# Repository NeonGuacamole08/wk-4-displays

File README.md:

# wk-4-displays

For the schematics and footprint, you will need:
| Component | KiCad Symbol | Footprint |
| :--- | :--- | :--- |
| **Microcontroller** | `Seeed_Studio_XIAO_Series:Seeed_XIAO_ESP32-C3` | `XIAO-ESP32-C3-SMD` |
| **LED Matrix Module Socket** | `Connector:Conn_01x05_Socket` | `Connector_PinSocket_2.54mm:PinSocket_1x05_P2.54mm_Vertical` |
| **Push Buttons (x3)** | `Switch:SW_Push` | `Button_Switch_THT:SW_PUSH_6mm` |
| **Rotary Encoder** | `Device:RotaryEncoder_Switch_MP` | `Rotary_Encoder:Rotary_Encoder_Alps_EC11E-Switch_Vertical_H20mm` |

I downloaded the footprints for my board here: https://github.com/Seeed-Studio/OPL_Kicad_Library/blob/master/Seeed%20Studio%20XIAO%20Series%20Library/XIAO-ESP32-C3-SMD.kicad_mod

## The Schematics:

- **A**: Add Symbol (Schematic Editor)
- **L**: Add Net Label (Schematic Editor)
- **E**: Edit Properties (Hover over any symbol or footprint and press E)

  1. Set up the XIAO ESP32-C3
   - Placed the XIAO ESP32-C3 microcontroller symbol on the canvas and assigned the official Seeed footprint (`XIAO-ESP32-C3-SMD`).

2. Added the LED Matrix Connector
   - Added a 5-pin female header socket (`Conn_01x05_Socket`) to connect the display module.
   - Connected hardware SPI pins (D7, D8, D10) plus power and ground using net labels to keep things clean.

3. Wired up the 10 µF Decoupling Capacitor
   - Placed a 10 µF capacitor across 5V and GND right near the matrix header to smooth out any power spikes from the LEDs.

4. Hooked up the 3 Push Buttons
   - Placed three push button symbols (`SW_Push`) with 6mm THT footprints.
   - Wired one side of each button to GND and the other side to individual GPIO pins (using `INPUT_PULLUP` in code so no extra resistors were needed).

5. Added the EC11 Rotary Encoder
   - Placed an EC11 encoder with switch symbol (`RotaryEncoder_Switch_MP`).
   - Wired pins A and B to digital GPIOs for rotation tracking, grounded common pin C and the mounting pins, and wired the built-in push switch (S1/S2) between a GPIO pin and GND.

6. Cleaned up with Net Labels
   - Used net labels across the whole sheet to keep the schematic tidy and easy to read without drawing long, crisscrossing wires.

## The PCB
Tip: You can use the "F" key to route your wiring using the shortest path
Trace your edge cuts, and you can even add some designs by using the image converter tool! 

You might need to play around with the size of your image!
1. Go to the image converter tool

2. Configure your image settings

3. Edit the size if needs be

4. Select "Footprint" as the output format (using the F.Cu layer), export to clipboard and paste in your PCB 

5. Paste on your PCB editor

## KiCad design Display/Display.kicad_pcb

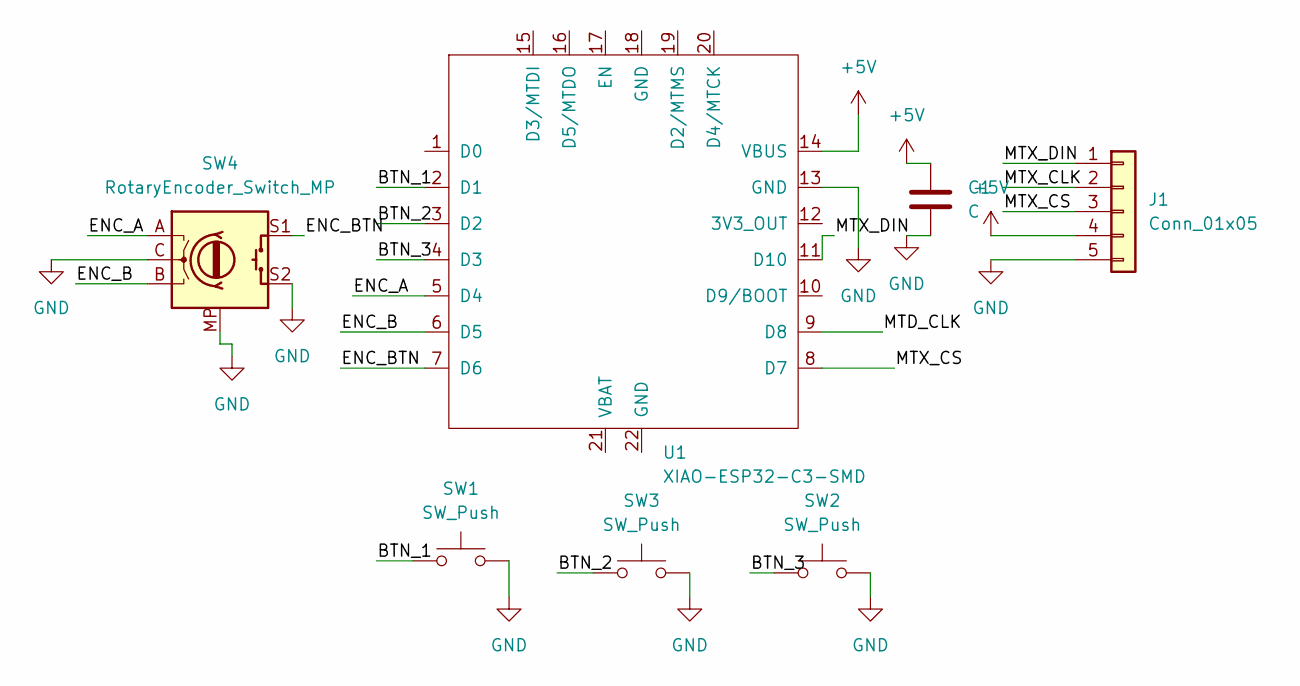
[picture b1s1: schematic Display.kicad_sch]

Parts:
C1: C; C_0805_2012Metric
J1: Conn_01x05; PinSocket_1x05_P2.54mm_Vertical
SW1, SW2, SW3: SW_Push; SW_PUSH_6mm
SW4: RotaryEncoder_Switch_MP; RotaryEncoder_Alps_EC11E-Switch_Vertical_H20mm
U1: XIAO-ESP32-C3-SMD

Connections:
+5V: C1.1, J1.4, U1.14 (VBUS)
/BTN_1: SW1.1, U1.2 (D1)
/BTN_2: SW3.1, U1.3 (D2)
/BTN_3: SW2.1, U1.4 (D3)
/ENC_A: SW4.A, U1.5 (D4)
/ENC_B: SW4.B, U1.6 (D5)
/ENC_BTN: SW4.S1, U1.7 (D6)
/MTD_CLK: U1.9 (D8)
/MTX_CLK: J1.2
/MTX_CS: J1.3, U1.8 (D7)
/MTX_DIN: J1.1, U1.11 (D10)
GND: C1.2, J1.5, SW1.2, SW2.2, SW3.2, SW4.C, SW4.MP, SW4.S2, U1.13 (GND)

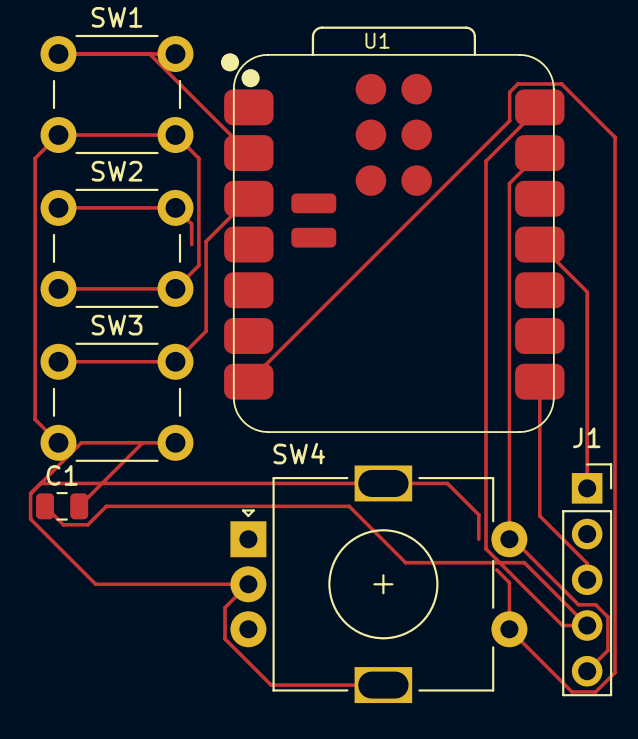
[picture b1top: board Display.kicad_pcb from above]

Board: 2 copper layers, 7 parts (0 on the bottom side), 10 nets.

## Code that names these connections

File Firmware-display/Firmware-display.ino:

#include <MD_Parola.h>
#include <MD_MAX72xx.h>
#include <SPI.h>

#define HARDWARE_TYPE MD_MAX72XX::FC16_HW
#define MAX_DEVICES 4
#define CS_PIN D7          // MTX_CS -> D7

const int BTN_1   = D0;    // Button 1 (SW1)
const int BTN_2   = D1;    // Button 2 (SW3)
const int BTN_3   = D2;    // Button 3 (SW2)
const int ENC_A   = D4;    // Encoder A
const int ENC_B   = D5;    // Encoder B
const int ENC_BTN = D6;    // Encoder Switch

MD_Parola display = MD_Parola(HARDWARE_TYPE, CS_PIN, MAX_DEVICES);

const char *messages[] = { "Hello!", "Make it yours", "8x8 forever" };
int current = 0;
int speed = 50;            
int intensity = 8;
textEffect_t effects[] = { PA_SCROLL_LEFT, PA_SCROLL_RIGHT, PA_OPENING };
int currentEffect = 0;

int lastA = HIGH;
int lastBtn1 = HIGH;
int lastBtn2 = HIGH;
int lastBtn3 = HIGH;
int lastEncBtn = HIGH;

unsigned long lastPress1 = 0;
unsigned long lastPress2 = 0;
unsigned long lastPress3 = 0;
unsigned long lastPressEnc = 0;

void setup() {
  pinMode(BTN_1, INPUT_PULLUP);
  pinMode(BTN_2, INPUT_PULLUP);
  pinMode(BTN_3, INPUT_PULLUP);
  pinMode(ENC_A, INPUT_PULLUP);
  pinMode(ENC_B, INPUT_PULLUP);
  pinMode(ENC_BTN, INPUT_PULLUP);
  
  display.begin();
  display.setIntensity(intensity);
  display.displayScroll(messages[current], PA_LEFT, effects[currentEffect], speed);
}

void loop() {
  // Encoder -> speed control
  int a = digitalRead(ENC_A);
  if (a != lastA && a == LOW) {
    speed += (digitalRead(ENC_B) == HIGH) ? -5 : 5;
    speed = constrain(speed, 10, 200);
    display.setSpeed(speed);
  }
  lastA = a;

  // Button 1 -> Next message
  int btn1 = digitalRead(BTN_1);
  if (btn1 == LOW && lastBtn1 == HIGH && millis() - lastPress1 > 200) {
    current = (current + 1) % 3;
    display.displayScroll(messages[current], PA_LEFT, effects[currentEffect], speed);
    lastPress1 = millis();
  }
  lastBtn1 = btn1;

  // Button 2 -> Cycle scroll effect
  int btn2 = digitalRead(BTN_2);
  if (btn2 == LOW && lastBtn2 == HIGH && millis() - lastPress2 > 200) {
    currentEffect = (currentEffect + 1) % 3;
    display.displayScroll(messages[current], PA_LEFT, effects[currentEffect], speed);
    lastPress2 = millis();
  }
  lastBtn2 = btn2;

  // Button 3 -> Cycle display brightness
  int btn3 = digitalRead(BTN_3);
  if (btn3 == LOW && lastBtn3 == HIGH && millis() - lastPress3 > 200) {
    intensity = (intensity >= 15) ? 4 : intensity + 4;
    display.setIntensity(intensity);
    lastPress3 = millis();
  }
  lastBtn3 = btn3;

  // Encoder Button -> Reset defaults
  int encBtn = digitalRead(ENC_BTN);
  if (encBtn == LOW && lastEncBtn == HIGH && millis() - lastPressEnc > 200) {
    speed = 50;
    intensity = 8;
    display.setSpeed(speed);
    display.setIntensity(intensity);
    lastPressEnc = millis();
  }
  lastEncBtn = encBtn;

  if (display.displayAnimate()) display.displayReset();
}
